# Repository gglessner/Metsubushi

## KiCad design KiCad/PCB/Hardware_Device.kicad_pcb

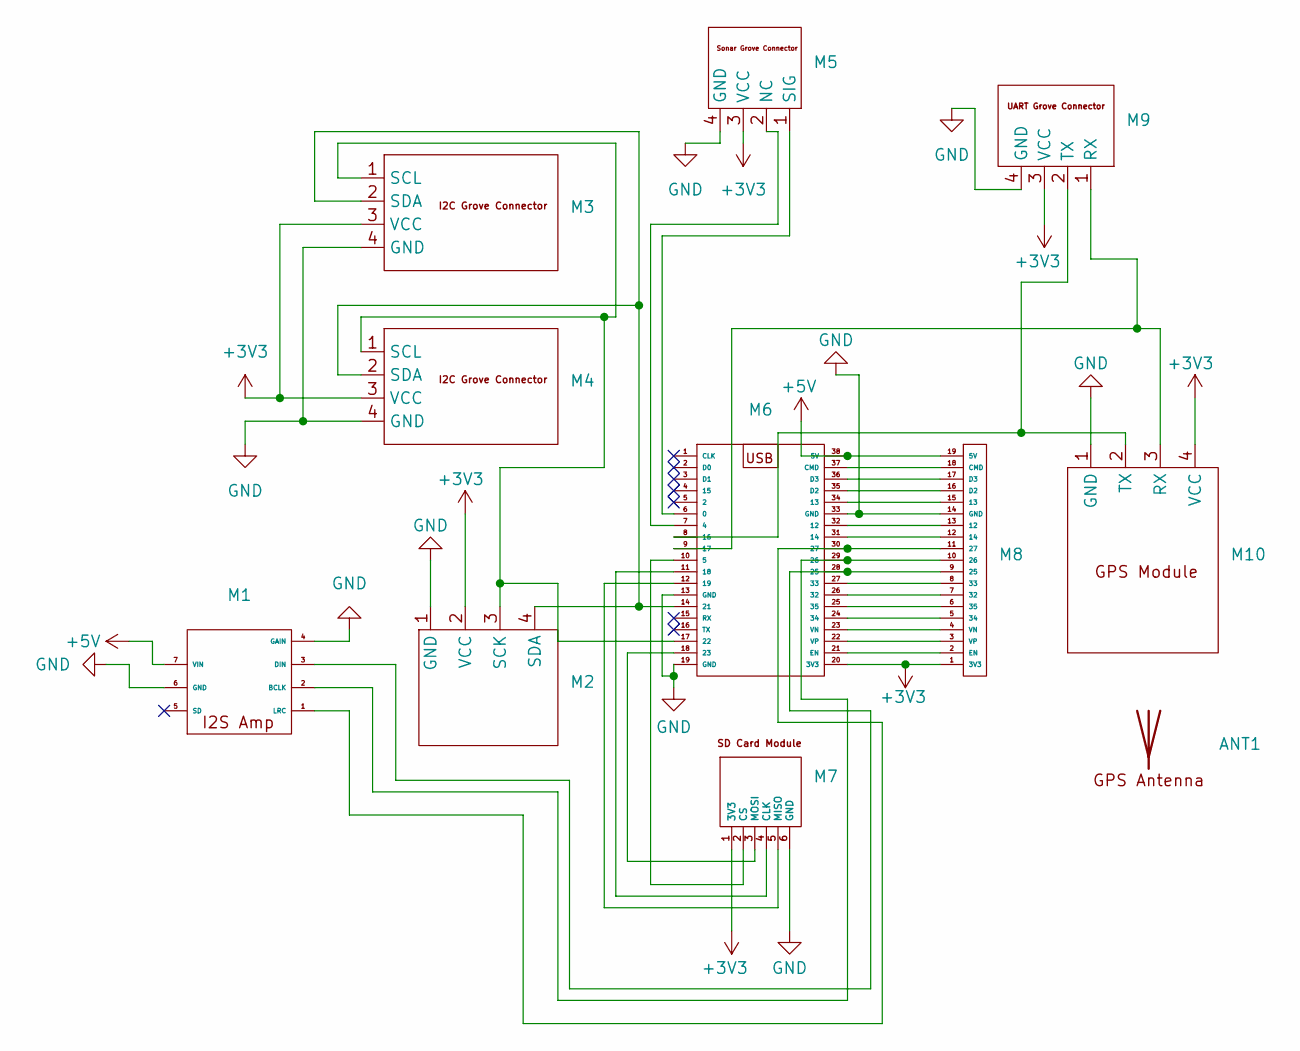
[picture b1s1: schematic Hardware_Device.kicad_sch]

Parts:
ANT1: GPS_Antenna
M1: I2S_Amp_updated
M2: OLED_I2C
M3, M4: I2C_updated
M5: Sonar_updated
M6: ESP-WROOM-32_Dev_Module_Narrow
M7: Micro_SD_Card_Adapter
M8: esp32_extra
M9: UART Grove Connector
M10: GY-GPS6MV2_Module

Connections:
+3V3: M2.2 (VCC), M3.3 (VCC), M4.3 (VCC), M5.3 (VCC), M6.20 (3V3), M7.1 (3V3), M8.1 (3V3), M9.3 (VCC), M10.4 (VCC)
+5V: M1.7 (VIN), M6.38 (5V), M8.19 (5V)
GND: M1.4 (GAIN), M1.6 (GND), M2.1 (GND), M3.4 (GND), M4.4 (GND), M5.4 (GND), M6.13 (GND), M6.19 (GND), M6.33 (GND), M7.6 (GND), M8.14 (GND), M9.4 (GND), M10.1 (GND)
unnamed: M1.2 (BCLK), M6.29 (26), M8.10 (26)
unnamed: M1.3 (DIN), M6.28 (25), M8.9 (25)
unnamed: M1.1 (LRC), M6.30 (27), M8.11 (27)
unnamed: M2.3 (SCK), M3.1 (SCL), M4.1 (SCL), M6.17 (22)
unnamed: M2.4 (SDA), M3.2 (SDA), M4.2 (SDA), M6.14 (21)
unnamed: M5.2 (NC), M6.7 (4)
unnamed: M5.1 (SIG), M6.6 (0)
unnamed: M6.10 (5), M7.2 (CS)
unnamed: M6.32 (12), M8.13 (12)
unnamed: M6.34 (13), M8.15 (13)
unnamed: M6.31 (14), M8.12 (14)
unnamed: M6.11 (18), M7.4 (CLK)
unnamed: M6.12 (19), M7.5 (MISO)
unnamed: M6.18 (23), M7.3 (MOSI)
unnamed: M6.26 (32), M8.7 (32)
unnamed: M6.27 (33), M8.8 (33)
unnamed: M6.24 (34), M8.5 (34)
unnamed: M6.25 (35), M8.6 (35)
unnamed: M6.37 (CMD), M8.18 (CMD)
unnamed: M6.35 (D2), M8.16 (D2)
unnamed: M6.36 (D3), M8.17 (D3)
unnamed: M6.21 (EN), M8.2 (EN)
unnamed: M6.23 (VN), M8.4 (VN)
unnamed: M6.22 (VP), M8.3 (VP)
unnamed: M6.9 (17), M9.1 (RX), M10.3 (RX)
unnamed: M6.8 (16), M9.2 (TX), M10.2 (TX)

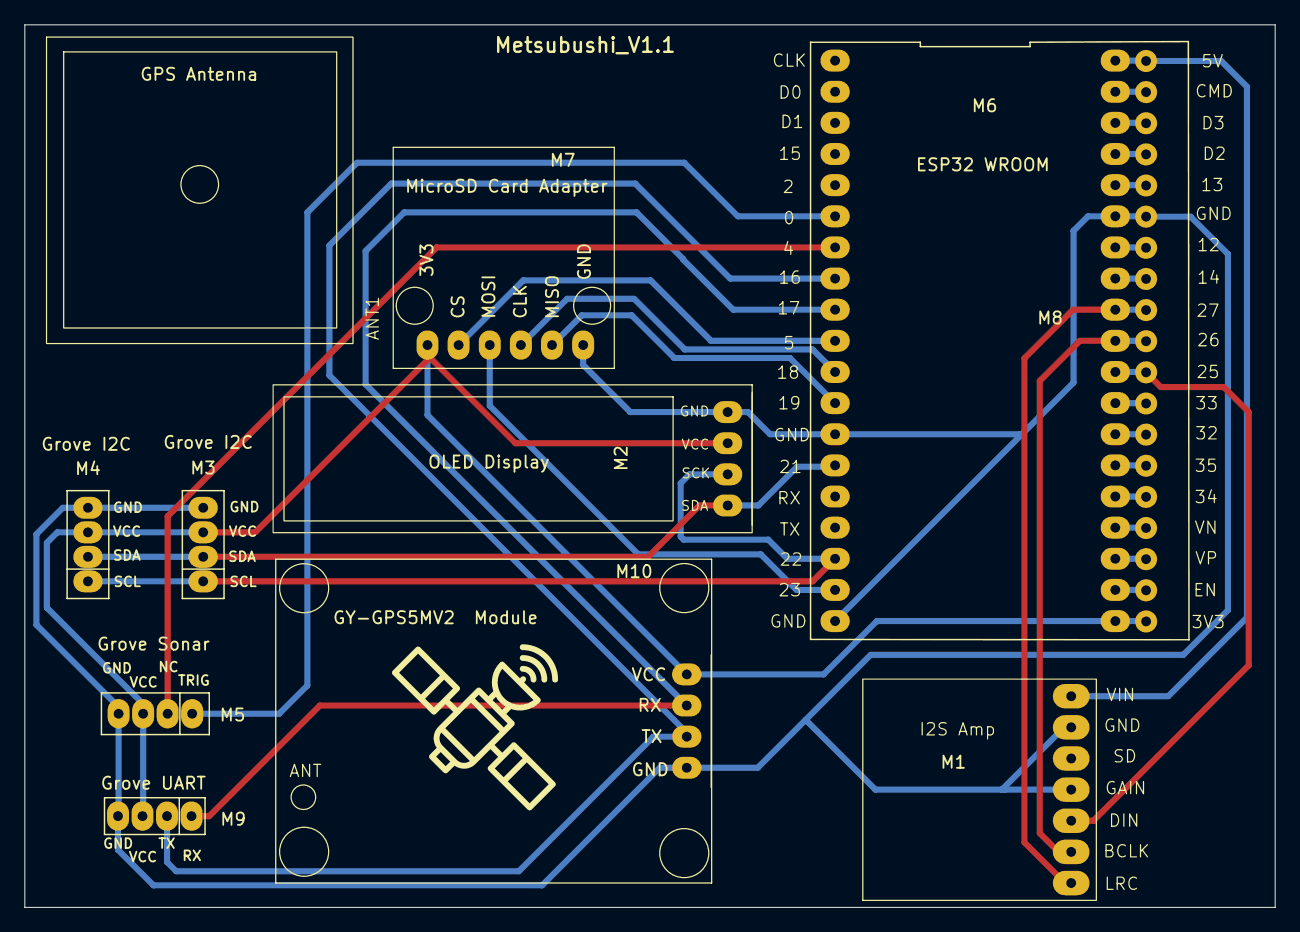
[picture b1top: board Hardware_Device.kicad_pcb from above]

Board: 2 copper layers, 102.0 x 72.0 mm, 11 parts (0 on the bottom side), 29 nets.

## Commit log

2024-06-26 Added Gerbers and Drill
    Initial commit of PCB design files for manufacturing.
2024-06-28 Initial Code Push
    Demo code for ESP32 hardware board.
2024-06-29 Added KiCard Design Files
    Added KiCard Design Files
2024-06-30 Update ESP32_EEPROM_Dumper.ino
    Updated to 1.0 with full functionality including I2C bus scanning
2024-06-30 Removed additional .DS_Store files
2024-07-01 Updated ESP32_EEPROM_Dumper to have I2C address lookup table
    Updated ESP32_EEPROM_Dumper to have I2C address lookup table
    Moved Code into directories
2024-07-02 Update ESP32_EEPROM_Dumper.ino
    Added compare file to EEPROM.
2024-07-02 Update ESP32_EEPROM_Dumper.ino
    Added Patch File on SD.
2024-07-24 Update to v1.4
    EEPROM writing now works.
    Patching a file now works.
